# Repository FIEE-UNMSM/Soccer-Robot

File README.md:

# ROBOT SOCCER 😸
> FROM IEEE RAS

## PROPOSITO
```bash
Las competiciones y torneos de robótica son puntos importantes que formentan la iniciativa de
construcción y mejora del armado de robots. IEEE RAS es una de los capítulos más preferibles
que lleva el ámbito de la robótica y la automatización a otro nivel. Por ello, se ha fomentado
la construcción de este repositorio para la mejora de uno de los robots más utilizado en las
competencias
```

## CONTENIDO

Se piensa implementar el contenido del modelado 3D, diseño del hardware y código fuente utilizados, y que son suficientes para que cualquier personas pueda implementar su propio robot soccer. Y así uno mismo pueda reconocer las mejoras y los cambios necesarios del robot, además de poder colaborar libremente con el repositorio :').

|CONTENIDO| SOFTWARE |
| ------ | ------ |
|Hardware||
|Código||
|Modelo 3D||

## AYUDANTES

Se agredece en gran manera a las personas que han contribuido con la mejora continua del repositorio.

| AYUDANTE | REDES SOCIALES |
| ------ | ------ |
|  |  |

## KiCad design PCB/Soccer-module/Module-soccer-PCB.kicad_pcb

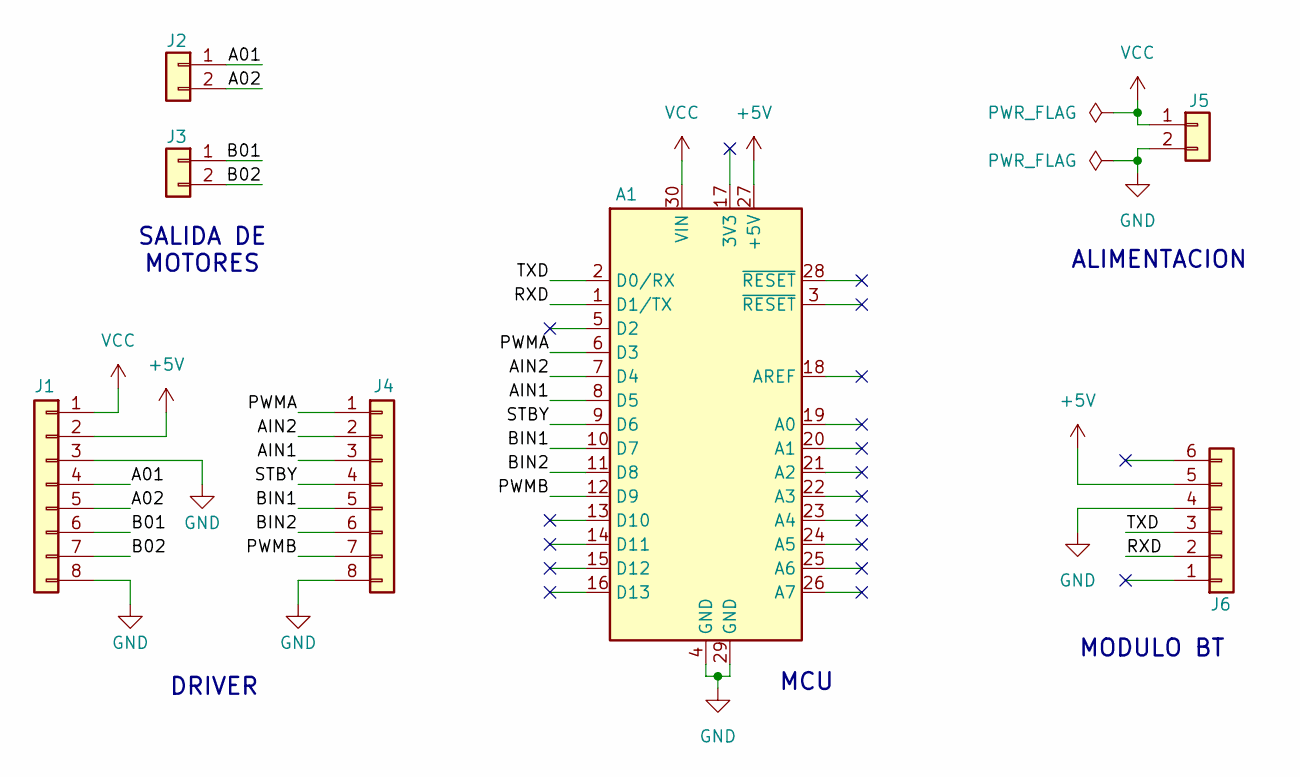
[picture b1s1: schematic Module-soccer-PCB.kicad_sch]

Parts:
A1: Arduino_Nano_v3.x; Arduino_Nano
J1, J4: Conn_01x08; PinSocket_1x08_P2.54mm_Vertical
J2, J3, J5: Conn_01x02; TerminalBlock_Phoenix_MKDS-1,5-2_1x02_P5.00mm_Horizontal
J6: Conn_01x06; PinSocket_1x06_P2.54mm_Vertical

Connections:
+5V: A1.27 (+5V), J1.2, J6.5
/A01: J1.4, J2.1
/A02: J1.5, J2.2
/AIN1: A1.8 (D5), J4.3
/AIN2: A1.7 (D4), J4.2
/B01: J1.6, J3.1
/B02: J1.7, J3.2
/BIN1: A1.10 (D7), J4.5
/BIN2: A1.11 (D8), J4.6
/PWMA: A1.6 (D3), J4.1
/PWMB: A1.12 (D9), J4.7
/RXD: A1.1 (D1/TX), J6.2
/STBY: A1.9 (D6), J4.4
/TXD: A1.2 (D0/RX), J6.3
GND: A1.4 (GND), A1.29 (GND), J1.3, J1.8, J4.8, J5.2, J6.4
VCC: A1.30 (VIN), J1.1, J5.1

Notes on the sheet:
DRIVER
ALIMENTACION
MCU
MODULO BT
SALIDA DE MOTORES

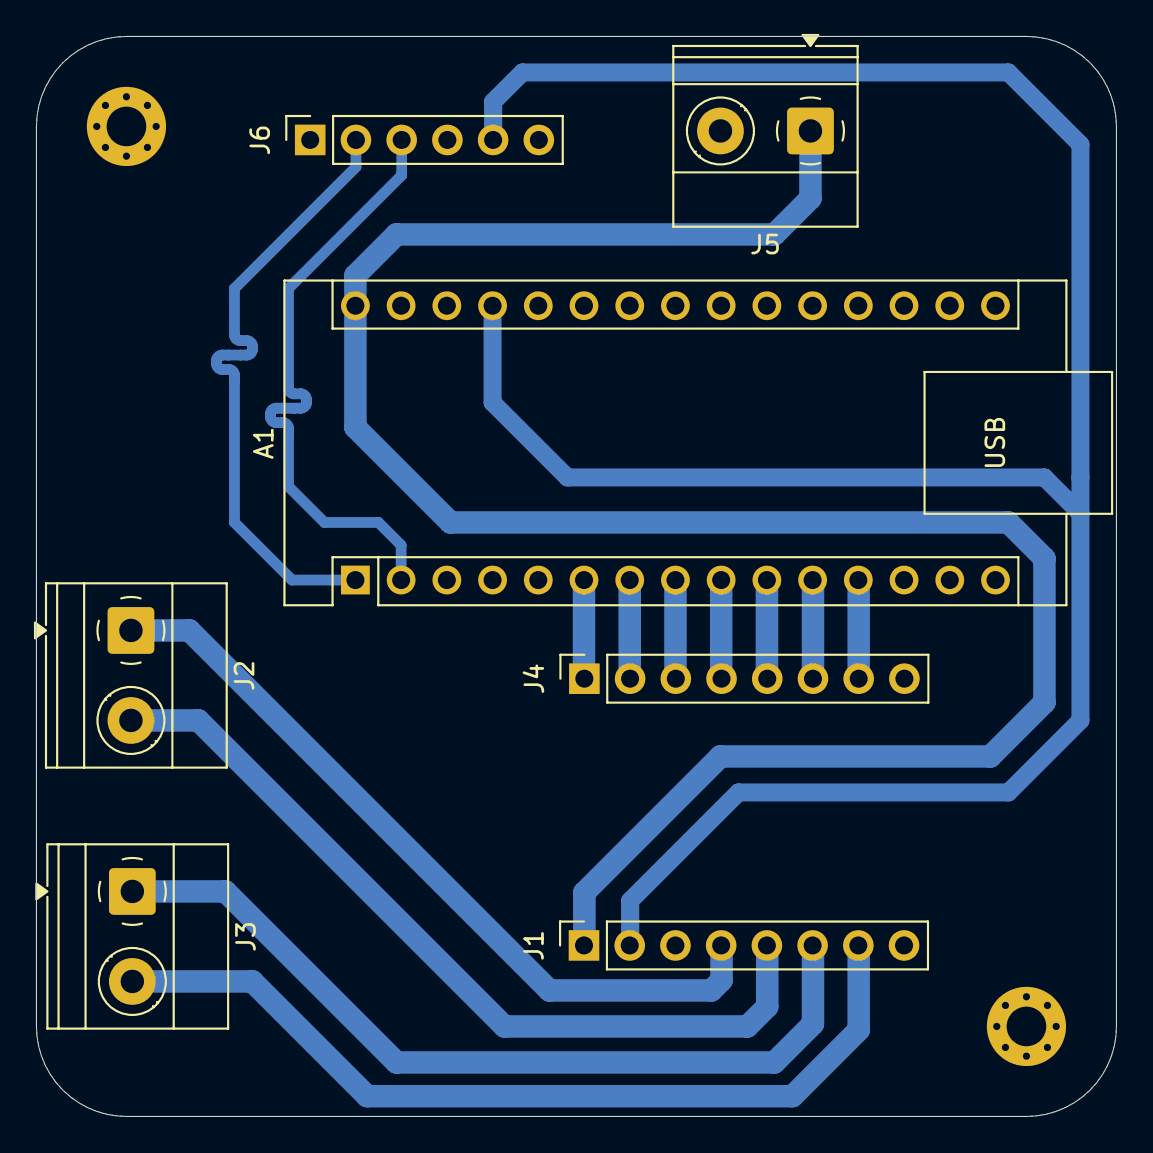
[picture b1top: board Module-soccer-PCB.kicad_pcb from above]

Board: 2 copper layers, 60.0 x 60.0 mm, 7 parts (0 on the bottom side), 16 nets.

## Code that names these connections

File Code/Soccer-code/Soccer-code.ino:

// CODIGO DE MOVIMIENTO PARA ROBOT SOCCER

#define PWMa 3  //Se define las variables a utilizar
#define AIN1 4
#define AIN2 5
#define STBY 6
#define BIN1 7
#define BIN2 8
#define PWMb 9

int instruction = "0";  //Se define la variable que almacena la instruccion

const int speedA = 255;  //Define la velocidad de los motores del par A
const int speedB = 255;  //Define la velocidad de los motores del par B

void setup() {
  Serial.begin(9600);  //Activa la comunicacion UART a 9600 baudios
  pinMode(PWMa, 1);   //Inicializan los pines de salida
  pinMode(AIN1, 1);
  pinMode(AIN2, 1);
  pinMode(STBY, 1);
  pinMode(BIN1, 1);
  pinMode(BIN2, 1);
  pinMode(PWMb, 1);

  digitalWrite(STBY,1);  //Inicializa el puente H
  analogWrite(PWMa, speedA);  //Establece la velocidad de los motores 
  analogWrite(PWMb, speedB);
}

void loop() {
  if(Serial.available()>0){  //Verifica si hay datos disponibles
    instruction = Serial.read();  //Lee la instrucción recibida
  }

  if(instruction == "1"){  //Instrucción para ADELANTE
    Move(1, 1, 0, 0);   
  }

  if(instruction == "2"){  //Instrucción para ATRÁS
    Move(0, 0, 1, 1);   
  }

  if(instruction == "3"){  //Instrucción para DERECHA
    Move(1, 0, 0, 1);  
  }

  if(instruction == "4"){  //Instrucción para IZQUIERDA
    Move(0, 1, 1, 0); 
  }

  if(instruction == "5"){  //Instrucción para ESTATICO
    Move(0, 0, 0, 0);
  }
}
//Funcion principal de MOVIMIENTO, basado en parámetros
void Move(const int SA1, const int SB1, const int SA2,const int SB2){
  digitalWrite(AIN1, SA1);
  digitalWrite(BIN1, SB1);
  digitalWrite(AIN2, SA2);
  digitalWrite(BIN2, SB2);
}

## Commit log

2025-03-19 Primer commit v0
2025-03-19 Implementacion de lineas V0.1
2025-03-19 Añade nuevos archivos para las líneas
2025-03-19 Pequena actualizacion
2025-03-19 README.md V1.0
    Mejora de la presentación.
2025-03-19 README.md V1.1
    Corrección de errores.
2025-03-30 Nuevos modelos del esquematico
2025-04-01 Mejoras de hardware
